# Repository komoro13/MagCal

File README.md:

# MagCal

**Non-contact magnetic thickness measurement system using a PIC24 microcontroller, Hall-effect sensing, custom PCB hardware, embedded C firmware, and calibration-based signal processing.**

MagCal was developed as a **CSCI 399 Independent Study** project at Hunter College.

The goal of the project is to estimate material thickness from changes in magnetic field strength rather than through a conventional mechanical caliper. The system measures the field produced by a controlled magnet/sensor geometry, processes the sensor output using the PIC24 ADC, applies calibration data, and displays the resulting thickness estimate on an LCD.

---

## Project Overview

MagCal combines:

- Embedded C firmware
- PIC24 microcontroller development
- Hall-effect sensing
- High-resolution ADC acquisition
- Custom PCB design
- Mechanical design
- Calibration and signal processing
- Drift and repeatability testing
- Low-voltage monitoring
- LCD-based user feedback

The complete project includes the firmware, KiCad hardware files, mechanical designs, production files, datasheets, and calibration datasets.

---

## Prototype

<p align="center">
  <em>Complete MagCal prototype showing the sensing probe, magnetic target, control electronics, LCD interface, and battery supply.</em>
</p>

## How It Works

MagCal measures material thickness using a **permanent magnet** on one side of the material and a **Hall-effect sensor** on the other.

The Hall sensor measures the magnetic field, which changes with the distance between the sensor and magnet. The **PIC24FJ128GC010** samples this signal using its internal ADC and averages **500 samples** to reduce noise.

The reading is normalized using the **far and close calibration points** and corrected for variations in the calibration span. The firmware then selects an experimentally generated calibration table and maps the reading to a thickness value displayed on the LCD.

<p align="center">
  <em>Measuring an acoustic guitar soundboard with the magnet inside the instrument and the sensing probe outside.</em>
</p>

<h2>Development</h2>

<div style="text-align: center; margin: 20px 0;">
  
  <p><em>Prototype development, debugging, and calibration work.</em></p>
</div>

## System Architecture

```text
      Permanent Magnet
             │
             │  Magnetic Field
             ▼
     Hall-Effect Sensor
             │
             │  Analog Voltage
             ▼
        PIC24FJ MCU
             │
        ┌────┴────┐
        │   ADC   │
        └────┬────┘
             │
      500-Sample Average
             │
      Baseline Correction
             │
      Gain Normalization
             │
     Calibration Lookup
             │
             ▼
      Thickness Estimate
             │
             ▼
            LCD
```

The firmware acquires sensor readings, averages multiple ADC samples, normalizes the measurement using close and far calibration baselines, selects the appropriate calibration dataset, and converts the normalized reading into a thickness estimate.

---
 
## Hardware

The electronics were designed as a custom PCB using **KiCad**.

The system includes:

- PIC24FJ microcontroller
- Hall-effect magnetic sensor
- Analog sensor interface
- LCD
- Status LEDs
- Calibration inputs
- Low-voltage detection
- Supporting power and passive circuitry

The PCB schematic, layout, Gerbers, and production outputs are available in:

```text
Hardware/
```

<h2>PCB Design</h2>

<p align="center">
  <em>KiCad 3D render of the MagCal PCB.</em>
</p>

## Firmware

The firmware is written in **embedded C** for the PIC24 platform.

Major responsibilities include:

- GPIO initialization
- ADC initialization and acquisition
- 500-sample averaging
- Close-baseline calibration
- Automatic far-baseline calibration
- Measurement normalization
- Gain correction
- Calibration-table selection
- Thickness lookup
- LCD output
- Low-voltage detection
- Watchdog servicing
- User feedback through status LEDs

The main measurement loop follows this sequence:

```text
Acquire averaged ADC reading
        ↓
Validate calibration state
        ↓
Normalize against far/close baselines
        ↓
Apply gain correction
        ↓
Select calibration table
        ↓
Map normalized value to thickness
        ↓
Display result
        ↓
Service watchdog
```

Firmware source is available under:

```text
Firmware/
```

---

## Measurement Averaging

Individual ADC samples contain enough variation to affect fine measurements.

Instead of using a single sample, MagCal averages **500 ADC readings** per measurement cycle.

```c
short int getAveragedReadings(void)
{
    long sum = 0;

    for (int i = 0; i < SAMPLING; i++)
    {
        sum += ADC16_read();
        __delay_ms(1);
    }

    return (short int)(sum / SAMPLING);
}
```

This reduces short-term measurement noise before calibration and thickness mapping are applied.

---

## Calibration System

Magnetic field strength does not vary linearly with distance, so a simple linear conversion between ADC reading and thickness is not sufficient.

MagCal therefore uses experimentally derived calibration data.

Each calibration point contains:

```c
typedef struct
{
    float threshold;
    float thickness;
} CalibrationPoint;
```

Calibration values are stored as lookup tables rather than large hard-coded conditional chains.

Example:

```c
static const CalibrationPoint calibration_990[] =
{
    {0.991f, 0.00f},
    {0.980f, 0.25f},
    {0.955f, 0.50f},
    {0.921f, 0.75f},
    {0.910f, 1.00f},
    ...
};
```

A generic lookup function then converts the normalized sensor reading into a thickness value:

```c
float mapReading(float reading,
                 const CalibrationPoint *table,
                 unsigned int size,
                 float maximum_thickness)
{
    for (unsigned int i = 0; i < size; i++)
    {
        if (reading >= table[i].threshold)
            return table[i].thickness;
    }

    return maximum_thickness;
}
```

This separates **calibration data** from the **mapping algorithm**, making the firmware easier to inspect, modify, and validate.

Calibration datasets are stored under:

```text
data/
```

---

## Baseline Calibration

The system uses two reference measurements:

- **Far baseline**
- **Close baseline**

These values define the working measurement span.

```c
normalized_result =
    (float)(result - baselineFar) /
    (float)(baselineClose - baselineFar);
```

The calculated span is then compared against the nominal calibration span to compensate for variation between calibration cycles.

```c
gain_correction =
    (baselineClose - baselineFar) /
    (float)CAL_SPAN;

normalized_result *= gain_correction;
```

The firmware also protects against a zero baseline span before performing normalization.

---

## Automatic Far-Baseline Detection

The firmware can automatically trigger far-baseline calibration when the measured ADC value enters the expected range.

```c
#define FAR_BASELINE_CALIBRATE_TRIGGER_THRESHOLD 10000
#define FAR_BASELINE_MIN 6400
#define FAR_BASELINE_MAX 7000
```

A candidate far-baseline measurement is accepted only if all sampled readings remain within the permitted range.

This helps reject invalid calibration attempts caused by incorrect magnet position or unexpected sensor values.

---

## Close Calibration

Close-baseline calibration is triggered by the calibration input:

```c
#define CLOSE_CALIBRATION_REQUESTED() (PORTEbits.RE7 == 1)
```

When calibration completes successfully, the device gives visual feedback through the status LEDs.

---

## ADC Debugging and MCU Errata

One of the most significant debugging challenges during the development of MagCal involved the PIC24FJ128GC010 ADC.

During early testing, the ADC produced unexpected readings that initially appeared to be caused by the Hall sensor, analog circuitry, or firmware configuration. Debugging therefore involved testing the measurement chain step by step and comparing the observed ADC behavior with the PIC24FJ128GC010 documentation and silicon errata.

The issue was eventually traced to documented device-specific ADC behavior rather than to the Hall sensor itself.

The PIC24FJ128GC010 is affected by **Erratum #5 in Table 2** of the device errata, concerning the ADC subsystem. The recommended workaround requires a hardware modification to the ADC reference circuitry.

The Microchip silicon errata document used during debugging is included in the [`Datasheets/`](Datasheets/) directory.

The modification was implemented directly on the PCB using a jumper wire, as shown below.

### Initial ADC Implementation

The first implementation used the PIC24's pipeline ADC. During testing, abnormal ADC behavior was observed over part of the expected input range.

This was particularly problematic for MagCal because the measurement depends on relatively small changes in the Hall sensor output. An ADC error that might be acceptable in another application could directly translate into an incorrect thickness measurement.

The problem was investigated by:

- Testing known and controlled ADC input conditions
- Comparing raw ADC values against the expected sensor behavior
- Checking the analog input configuration
- Verifying ADC initialization and reference configuration
- Reviewing the PIC24FJ128GC010 datasheet and silicon errata
- Separating sensor behavior from ADC behavior during testing

The investigation showed that the unexpected measurements were related to documented ADC limitations/errata of the microcontroller.

---

### Moving to the 16-bit Sigma-Delta ADC

To improve the measurement path, the design was moved to the PIC24FJ128GC010's **16-bit Sigma-Delta ADC** using a differential measurement configuration.

The firmware was updated accordingly, including the ADC initialization sequence and readiness/calibration handling required by the peripheral.

This provided a more suitable acquisition path for the low-frequency precision measurement performed by MagCal.

The Hall sensor signal is sampled repeatedly and the resulting ADC measurements are averaged before being used by the calibration algorithm.

---

### ADC Reference / REFPUMP Issue

Another important issue involved the ADC reference circuitry.

During debugging, incorrect or unstable ADC behavior was traced to the reference configuration required by the Sigma-Delta ADC. The PIC24FJ128GC010 documentation and errata were used to determine the required hardware configuration.

A hardware modification was therefore made to the existing PCB rather than manufacturing a completely new revision of the board.

A small jumper was added to implement the required reference connection.

### Hardware Modification

<p align="center">
  <em>Hardware modification implementing the PIC24FJ128GC010 ADC errata workaround.</em>
</p>

This modification is intentionally visible in the project documentation because it represents an important part of the engineering process: identifying a silicon/device-specific problem, finding the relevant information in the manufacturer's documentation, and implementing a hardware-level correction on an already fabricated PCB.

---

### ADC Initialization

The ADC firmware also had to account for the peripheral's required initialization and calibration sequence.

In particular, ADC operation could not simply begin immediately after enabling the peripheral. The firmware had to wait for the appropriate ADC ready/calibration state before measurements could be considered valid.

This was incorporated into the ADC initialization code in:

```text
Firmware/ADC.c
```

---

### Debugging Outcome

Resolving the ADC problems required debugging across several layers of the system:

```text
Hall Sensor
     │
     ▼
Analog Signal
     │
     ▼
PCB / Reference Circuitry
     │
     ▼
PIC24 ADC Hardware
     │
     ▼
ADC Configuration
     │
     ▼
Raw ADC Samples
     │
     ▼
Averaging / Calibration
     │
     ▼
Thickness Measurement
```

Rather than compensating for the unexpected readings in software, the underlying ADC and reference problems were investigated and corrected.

This debugging process was one of the most important parts of the project because it required working across **firmware, analog electronics, PCB hardware, microcontroller documentation, and silicon errata** rather than treating each area independently.

## Sensor Drift

Hall-effect measurements change slightly while the electronics reach thermal equilibrium.

The system was experimentally characterized for:

- Warm-up behavior
- Baseline drift
- Measurement repeatability
- Sensor-to-magnet positioning sensitivity

These observations influenced both the calibration process and the firmware design.

## Mechanical Design

Because magnetic field strength depends strongly on geometry, mechanical repeatability is important to measurement consistency.

Custom mechanical components were designed to maintain repeatable positioning between:

- Hall sensor
- Magnet
- Measured material

Mechanical designs and printable models are available in:

```text
Mechanical/
```

### Probe Mechanical Render

<p align="center">
  <em>FreeCAD render of the MagCal sensing probe enclosure.</em>
</p>

## Low-Voltage Protection

The system uses the PIC24 high/low-voltage detection functionality to detect insufficient battery voltage.

When low voltage is detected, the firmware disables further HLVD interrupts, informs the user through the LCD, and remains in a safe watchdog-serviced state.

```c
void __attribute__((interrupt, no_auto_psv)) _LVDInterrupt(void)
{
    IEC4bits.HLVDIE = 0;
    IFS4bits.HLVDIF = 0;

    LCD_print_string("Change battery", 0);

    while (1)
    {
        ClrWdt();
    }
}
```

---

## Repository Structure

```text
MagCal/
├── Firmware/        PIC24 embedded C firmware
├── Hardware/        KiCad schematic, PCB and production files
├── Mechanical/      Mechanical CAD and printable models
├── data/            Calibration and measurement datasets
├── Datasheets/      Component documentation
├── Libs/            Supporting design libraries
├── docs/
│   └── images/      README photos, renders and plots
└── README.md
```

---

## Tools and Technologies

### Firmware

- Embedded C
- PIC24FJ
- MPLAB X
- XC16
- ADC acquisition
- Watchdog timer
- HLVD interrupt handling
- LCD interfacing

### Hardware

- KiCad
- PCB design
- PCB fabrication
- Hall-effect sensing
- Analog measurement
- Component-level debugging
- Soldering and PCB rework

### Mechanical / Experimental

- FreeCAD
- 3D printing
- Sensor characterization
- Calibration
- Repeatability testing
- Drift analysis

---

## Engineering Takeaways

This project involved considerably more than reading a sensor and displaying a value.

Some of the main engineering lessons included:

- Debugging hardware and firmware as a single system
- Reading and applying microcontroller errata
- Characterizing analog sensor behavior experimentally
- Designing calibration around real-world sensor variation
- Separating calibration data from firmware logic
- Reducing measurement noise through sampling and averaging
- Designing mechanical geometry for repeatable measurements
- Producing custom PCB hardware alongside firmware
- Building fault handling into an embedded system

---

## Project Status

MagCal has progressed through:

- Hardware design
- PCB fabrication
- Firmware development
- Sensor integration
- ADC debugging
- Mechanical prototyping
- Calibration
- Drift characterization
- Measurement testing

The current firmware uses multiple calibration tables selected according to baseline conditions.

Further work may include:

- Additional calibration refinement
- Temperature/drift compensation
- Improved mechanical repeatability
- Further validation of measurement accuracy and resolution

---

## Author

**Theodoros Bogiatzis**  
Computer Science  
Hunter College, CUNY

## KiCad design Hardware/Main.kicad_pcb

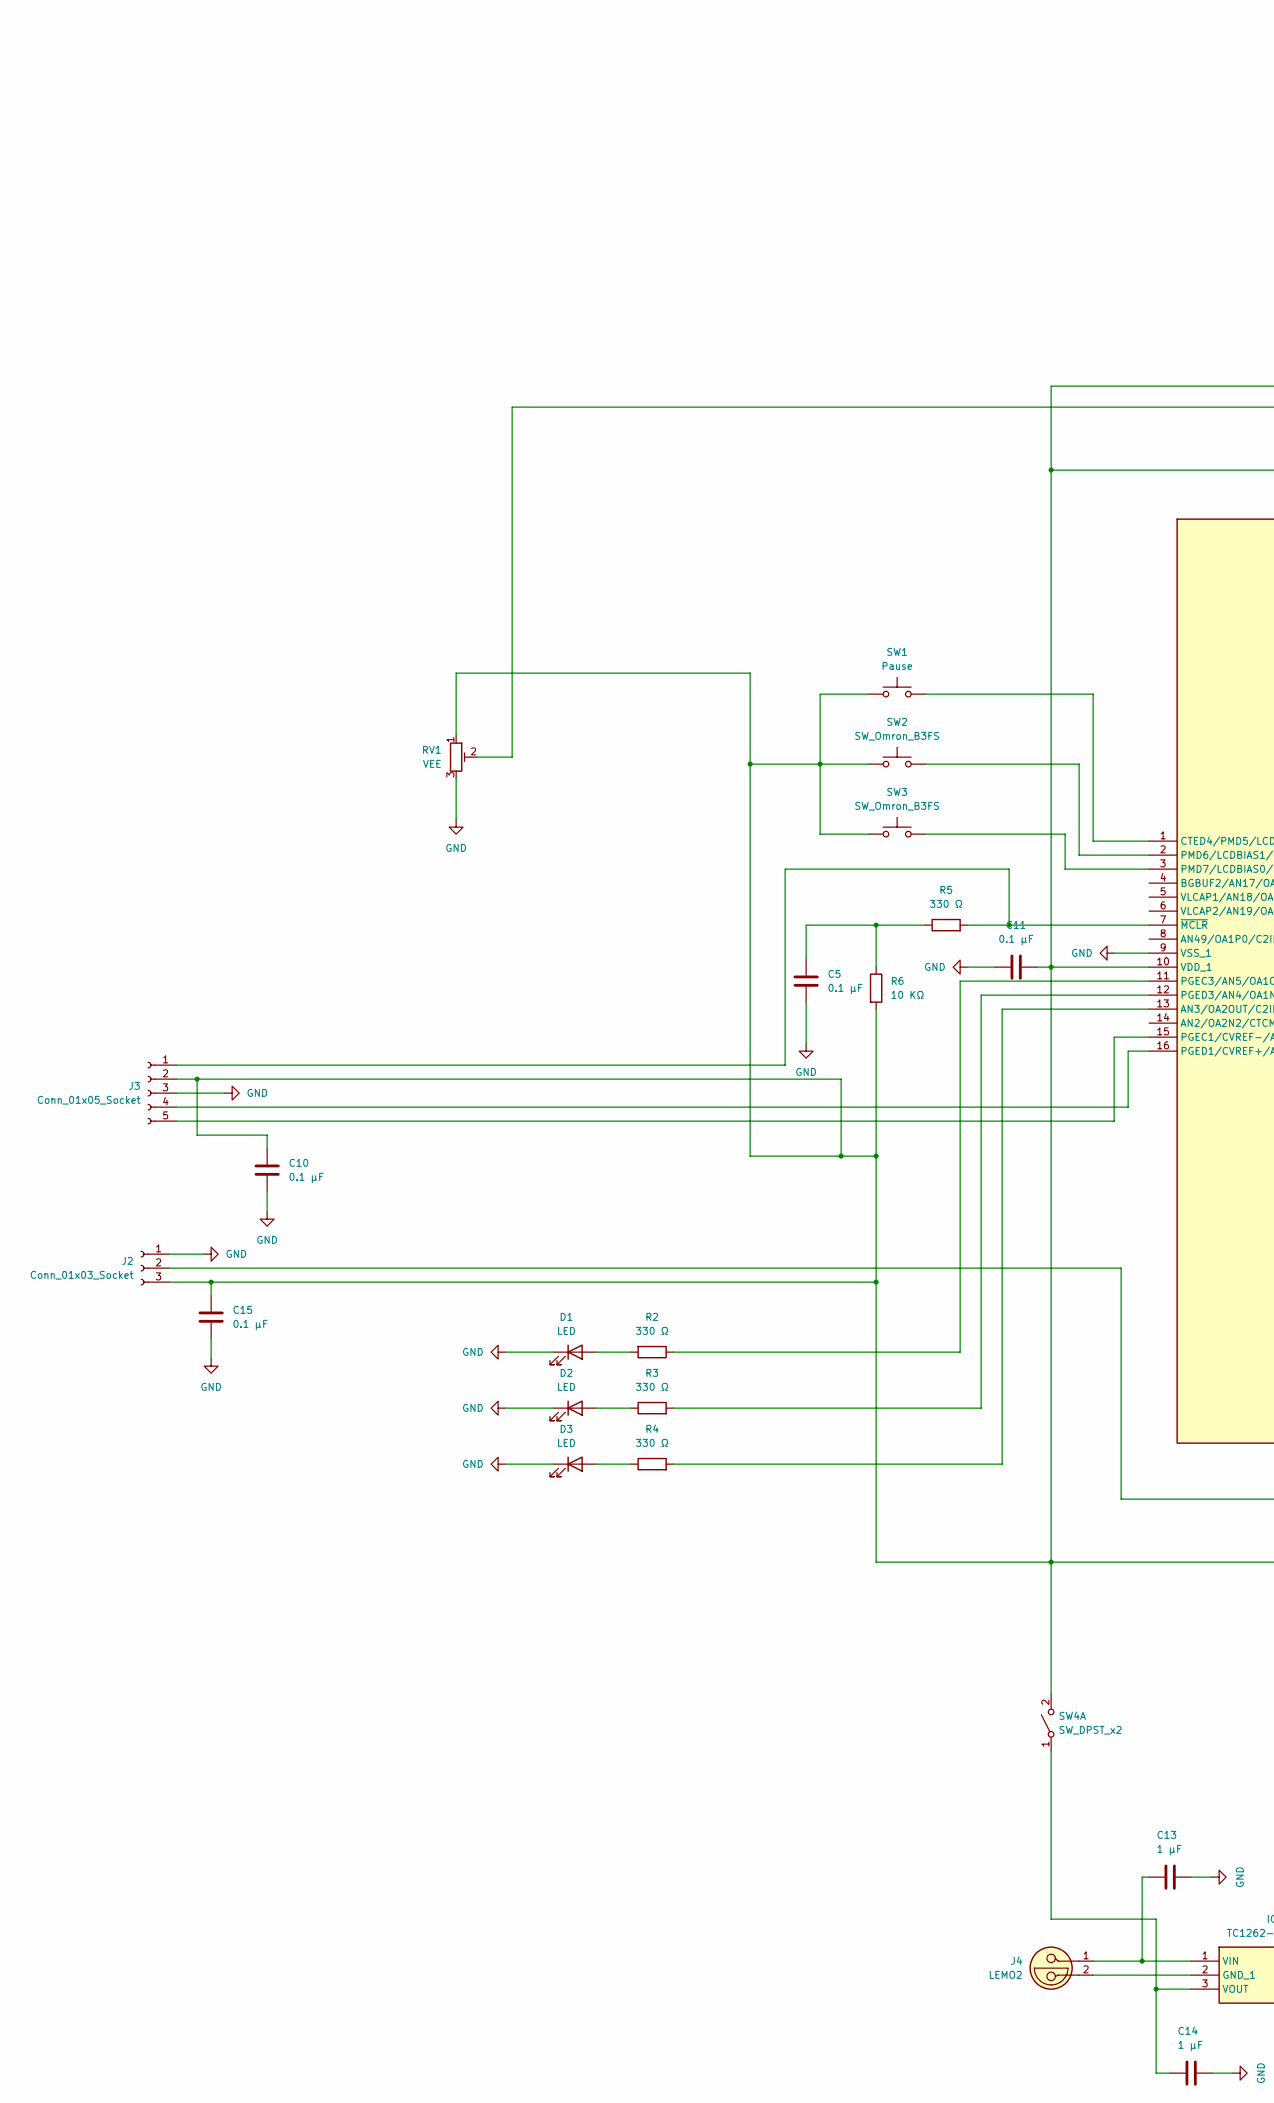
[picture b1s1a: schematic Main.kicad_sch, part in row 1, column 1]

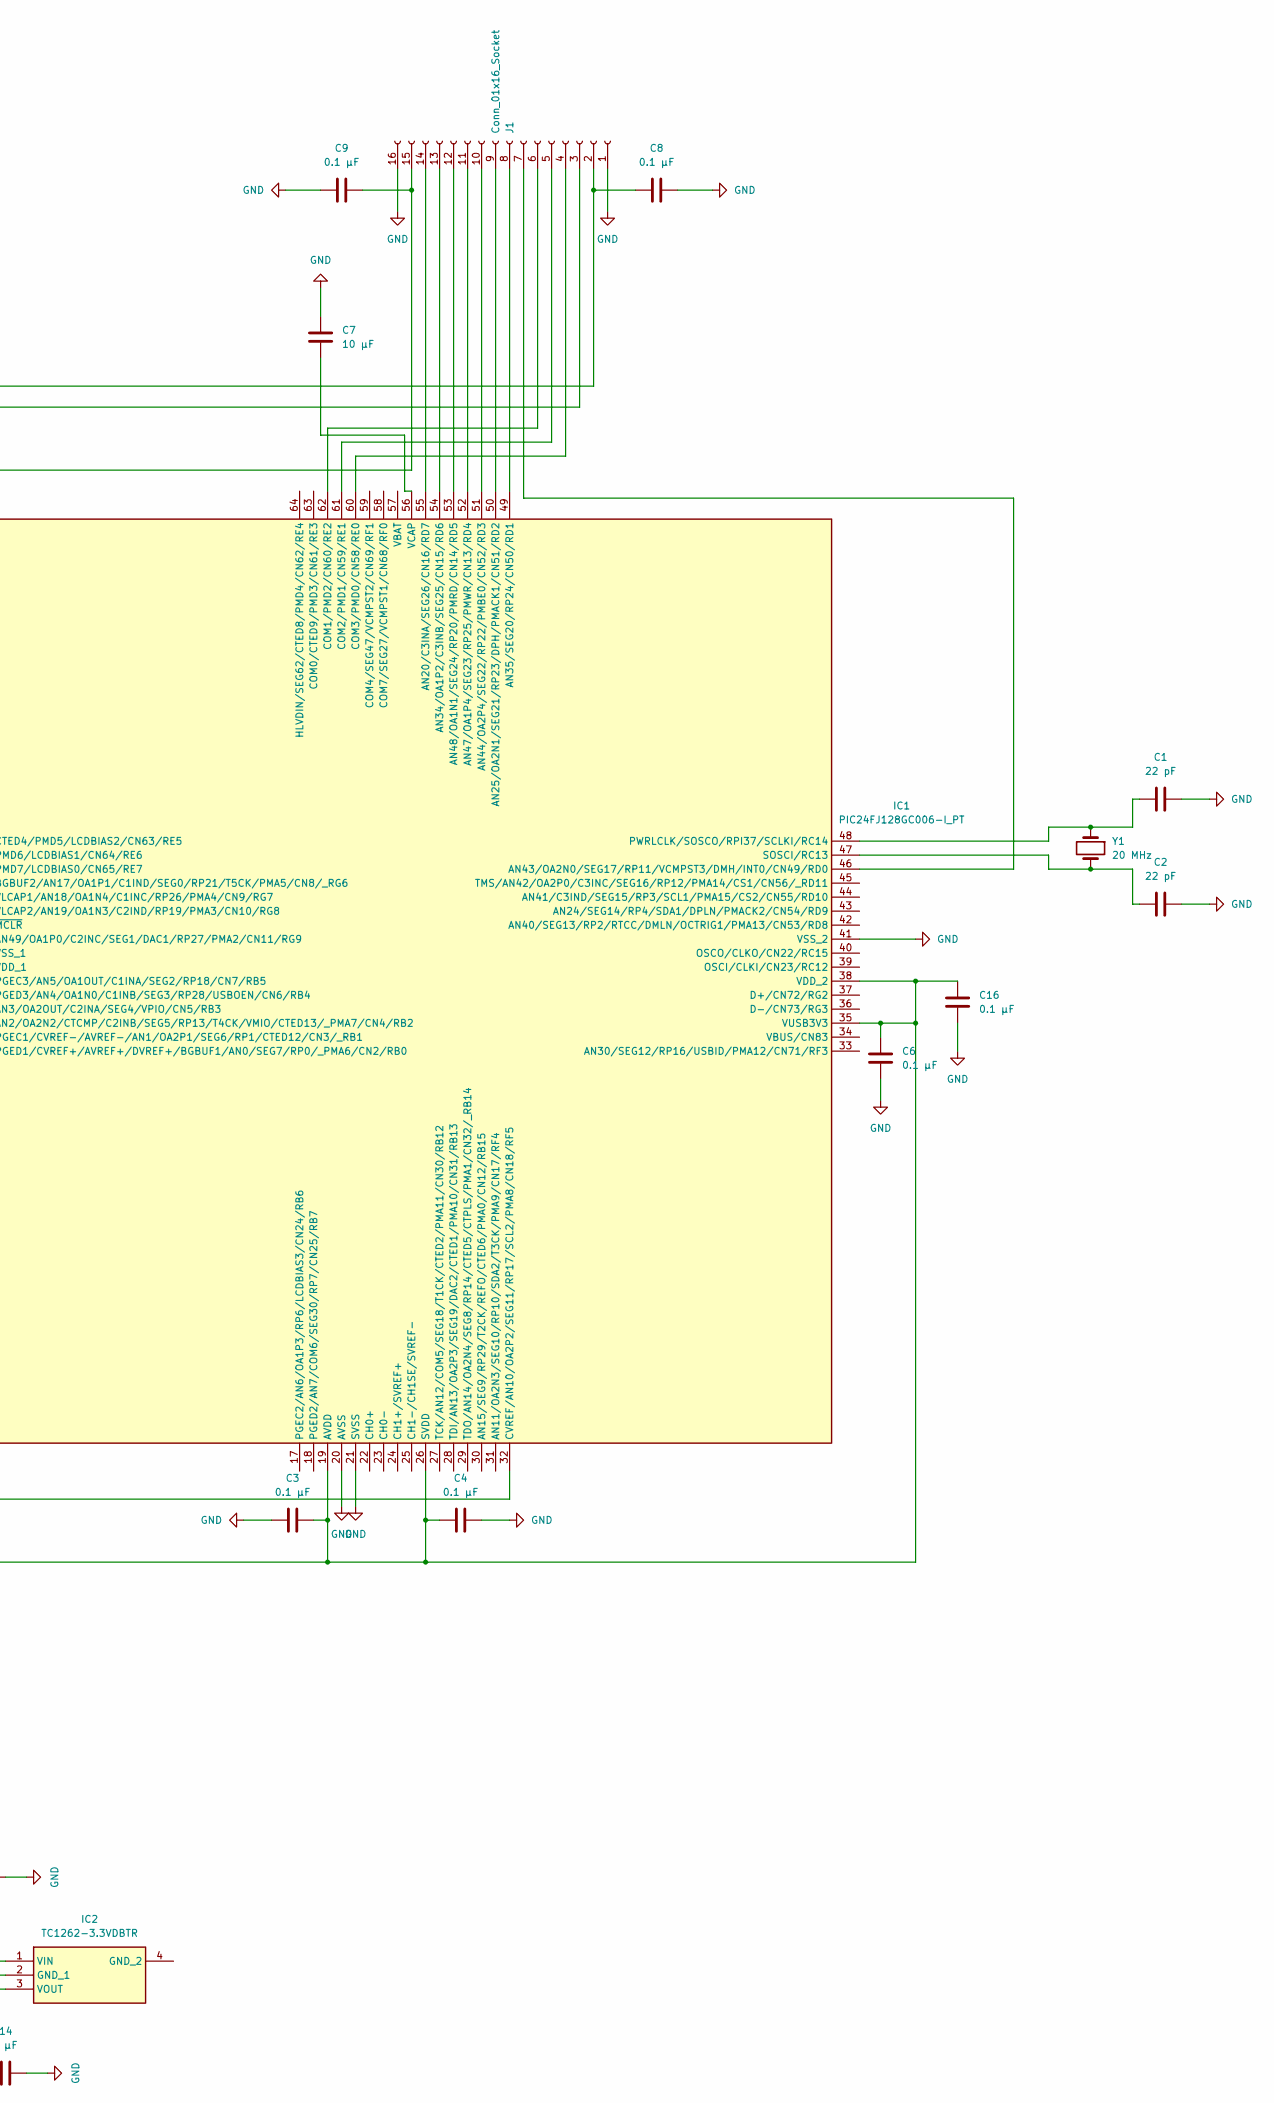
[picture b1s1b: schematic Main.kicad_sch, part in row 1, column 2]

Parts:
C1, C2: 22 pF; C_0402_1005Metric; LCSC Part Number C1555
C3, C4, C5, C6, C8, C9, C10, C11: 0.1 μF; C_0201_0603Metric
C7: 10 μF; C_0805_2012Metric
C13: 1 μF; C_0201_0603Metric; LCSC Part Number C17414
C14: 1 μF; C_0201_0603Metric; LCSC Part Number C5205032
C15, C16: 0.1 μF; C_0402_1005Metric
D1, D2, D3: LED; LED_Everlight-SMD3528_3.5x2.8mm_67-21ST; LCSC Part Number C635577
IC1: PIC24FJ128GC006-I_PT; QFP50P1200X1200X120-64N; Manufacturer_Part_Number PIC24FJ128GC006-I/PT; Mouser Part Number 579-P24FJ128GC006IPT
IC2: TC1262-3.3VDBTR; SOT230P700X180-4N; Manufacturer_Part_Number TC1262-3.3VDBTR; Mouser Part Number 579-TC1262-3.3VDBTR
J1: Conn_01x16_Socket; PinHeader_1x16_P2.54mm_Vertical; LCSC Part Number C722171
J2: Conn_01x03_Socket; PinHeader_1x03_P2.54mm_Vertical; LCSC Part Number C90471
J3: Conn_01x05_Socket; PinHeader_1x05_P2.54mm_Vertical; LCSC Part Number C5360898
J4: LEMO2; PinHeader_1x02_P2.54mm_Vertical; LCSC Part Number C5336507
R2, R3, R4: 330 Ω; R_0402_1005Metric; LCSC Part Number C156103
R5: 330 Ω; R_0402_1005Metric
R6: 10 ΚΩ; R_1206_3216Metric
RV1: VEE; Potentiometer_Runtron_RM-063_Horizontal; LCSC Part Number C146243
SW1: Pause; SW_PUSH-12mm; LCSC Part Number C1740
SW2, SW3: SW_Omron_B3FS; SW_PUSH-12mm; LCSC Part Number C342623
SW4: SW_DPST_x2; PinHeader_1x02_P2.54mm_Vertical; LCSC Part Number C5205032
Y1: 20 MHz; Crystal_HC18-U_Vertical; LCSC Part Number C49661

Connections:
unnamed: C5.1, R5.1, R6.1
unnamed: D1.2 (A), R2.2
unnamed: D2.2 (A), R3.1
unnamed: D3.2 (A), R4.1
unnamed: IC1.13 (AN3/OA2OUT/C2INA/SEG4/VPIO/CN5/RB3), R4.2
unnamed: IC1.55 (AN20/C3INA/SEG26/CN16/RD7), J1.14
unnamed: IC1.50 (AN25/OA2N1/SEG21/RP23/DPH/PMACK1/CN51/R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), J1.9
unnamed: IC1.54 (AN34/OA1P2/C3INB/SEG25/CN15/RD6), J1.13
unnamed: IC1.49 (AN35/SEG20/RP24/CN50/RD1), J1.8
unnamed: IC1.46 (AN43/OA2N0/SEG17/RP11/VCMPST3/DMH/INT0/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), J1.7
unnamed: IC1.51 (AN44/OA2P4/SEG22/RP22/PMBE0/CN52/RD3), J1.10
unnamed: IC1.52 (AN47/OA1P4/SEG23/RP25/PMWR/CN13/RD4), J1.11
unnamed: IC1.53 (AN48/OA1N1/SEG24/RP20/PMRD/CN14/RD5), J1.12
unnamed: C3.2, C4.1, C6.1, C8.1, C9.2, C10.1, C11.2, C15.1, C16.1, IC1.10 (VDD_1), IC1.19 (AVDD), IC1.26 (SVDD), IC1.35 (VUSB3V3), IC1.38 (VDD_2), J1.2, J1.15, J2.3, J3.2, R6.2, RV1.1, SW1.1, SW2.1, SW3.1, SW4.2 (B)
unnamed: IC1.62 (COM1/PMD2/CN60/RE2), J1.6
unnamed: IC1.61 (COM2/PMD1/CN59/RE1), J1.5
unnamed: IC1.60 (COM3/PMD0/CN58/RE0), J1.4
unnamed: IC1.1 (CTED4/PMD5/LCDBIAS2/CN63/RE5), SW1.2
unnamed: IC1.32 (CVREF/AN10/OA2P2/SEG11/RP17/SCL2/PMA8/C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), J2.2
unnamed: IC1.15 (PGEC1/CVREF-/AVREF-/AN1/OA2P1/SEG6/RP1/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), J3.5
unnamed: IC1.11 (PGEC3/AN5/OA1OUT/C1INA/SEG2/RP18/CN7/RB5), R2.1
unnamed: IC1.16 (PGED1/CVREF+/AVREF+/DVREF+/BGBUF1/AN0/S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), J3.4
unnamed: IC1.12 (PGED3/AN4/OA1N0/C1INB/SEG3/RP28/USBOEN/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), R3.2
unnamed: IC1.2 (PMD6/LCDBIAS1/CN64/RE6), SW2.2
unnamed: IC1.3 (PMD7/LCDBIAS0/CN65/RE7), SW3.2
unnamed: C1.1, IC1.48 (PWRLCLK/SOSCO/RPI37/SCLKI/RC14), Y1.1
unnamed: C2.1, IC1.47 (SOSCI/RC13), Y1.2
unnamed: C7.2, IC1.56 (VCAP)
unnamed: IC1.7 (~MCLR), J3.1, R5.2
unnamed: C13.1, IC2.1 (VIN), J4.1
unnamed: C14.1, IC2.3 (VOUT), SW4.1 (A)
unnamed: J1.3, RV1.2

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
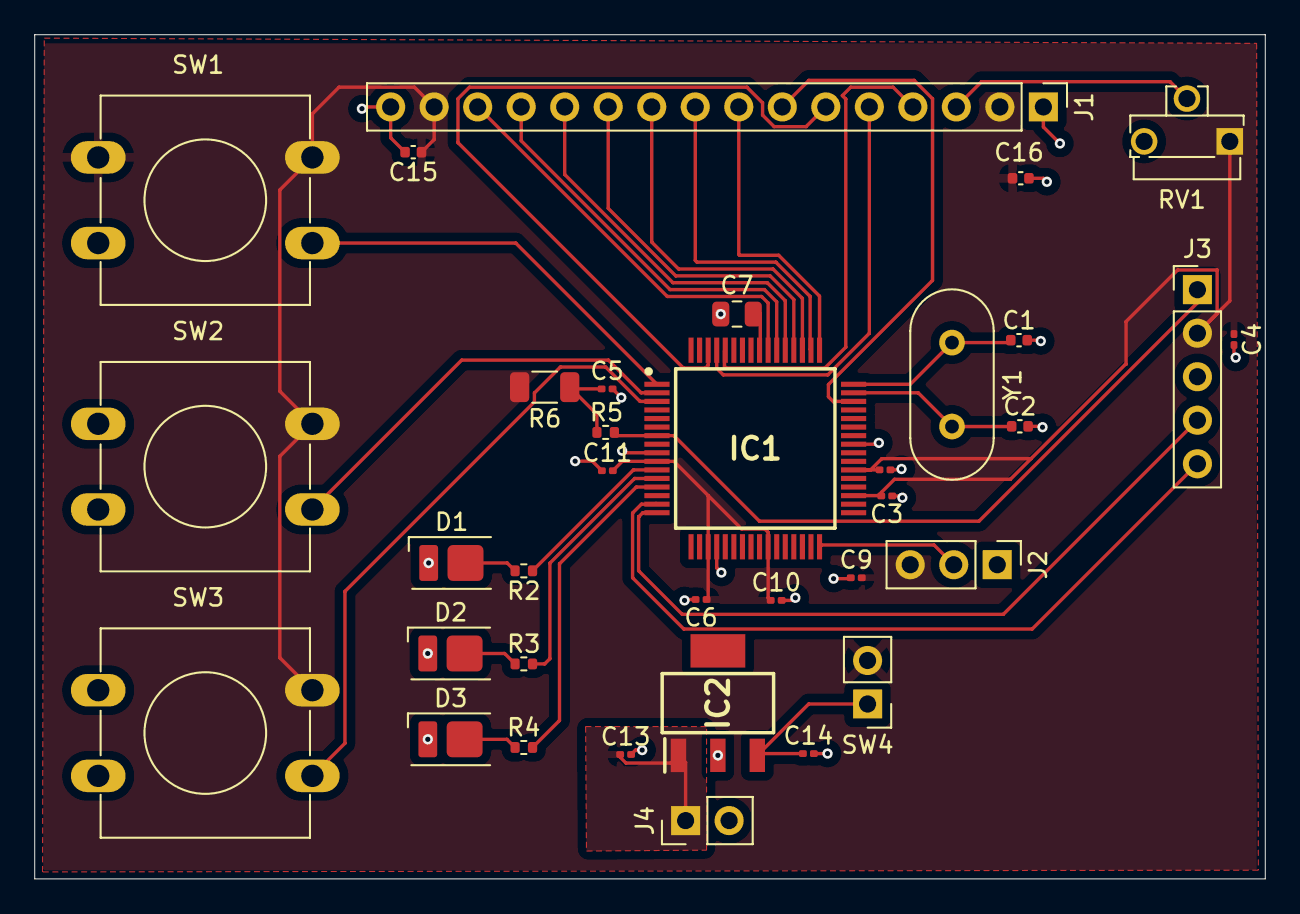
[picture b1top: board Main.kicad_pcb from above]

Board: 2 copper layers, 71.8 x 49.3 mm, 35 parts (0 on the bottom side), 33 nets.

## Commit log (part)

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2024-12-11 added source
2024-12-12 lang
2024-12-28 added pcb
2025-01-03 added main pcb
2025-01-03 fixed sensor PCB
2025-01-03 fixed main pcb
2025-01-04 printed PCBs
2025-01-10 changed pcb
